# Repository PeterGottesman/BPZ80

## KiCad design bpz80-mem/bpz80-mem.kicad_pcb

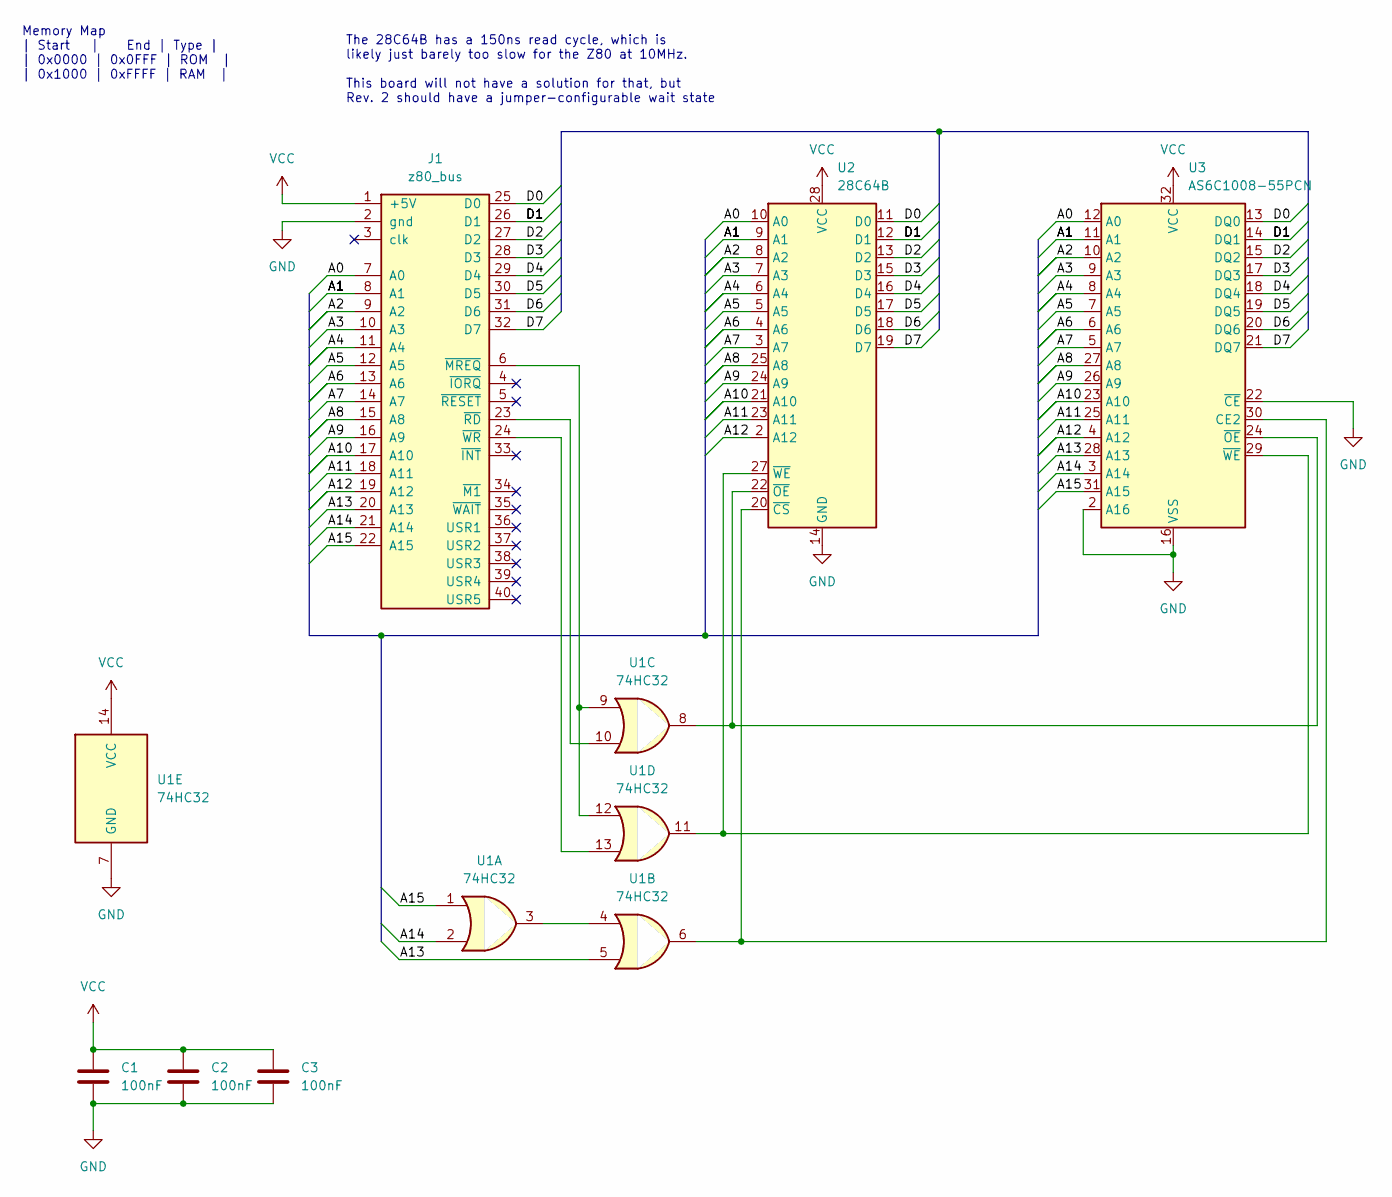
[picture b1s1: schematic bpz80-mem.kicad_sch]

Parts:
C1, C2, C3: 100nF; C_Disc_D5.0mm_W2.5mm_P5.00mm
J1: z80_bus; PinHeader_2x20_P2.54mm_Horizontal
U1: 74HC32; DIP-14_W7.62mm_Socket
U2: 28C64B; DIP-28_W15.24mm_Socket
U3: AS6C1008-55PCN; DIP-32_W15.24mm_Socket

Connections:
/A0: J1.7 (A0), U2.10 (A0), U3.12 (A0)
/A1: J1.8 (A1), U2.9 (A1), U3.11 (A1)
/A2: J1.9 (A2), U2.8 (A2), U3.10 (A2)
/A3: J1.10 (A3), U2.7 (A3), U3.9 (A3)
/A4: J1.11 (A4), U2.6 (A4), U3.8 (A4)
/A5: J1.12 (A5), U2.5 (A5), U3.7 (A5)
/A6: J1.13 (A6), U2.4 (A6), U3.6 (A6)
/A7: J1.14 (A7), U2.3 (A7), U3.5 (A7)
/A8: J1.15 (A8), U2.25 (A8), U3.27 (A8)
/A9: J1.16 (A9), U2.24 (A9), U3.26 (A9)
/A10: J1.17 (A10), U2.21 (A10), U3.23 (A10)
/A11: J1.18 (A11), U2.23 (A11), U3.25 (A11)
/A12: J1.19 (A12), U2.2 (A12), U3.4 (A12)
/A13: J1.20 (A13), U1.5, U3.28 (A13)
/A14: J1.21 (A14), U1.2, U3.3 (A14)
/A15: J1.22 (A15), U1.1, U3.31 (A15)
/D0: J1.25 (D0), U2.11 (D0), U3.13 (DQ0)
/D1: J1.26 (D1), U2.12 (D1), U3.14 (DQ1)
/D2: J1.27 (D2), U2.13 (D2), U3.15 (DQ2)
/D3: J1.28 (D3), U2.15 (D3), U3.17 (DQ3)
/D4: J1.29 (D4), U2.16 (D4), U3.18 (DQ4)
/D5: J1.30 (D5), U2.17 (D5), U3.19 (DQ5)
/D6: J1.31 (D6), U2.18 (D6), U3.20 (DQ6)
/D7: J1.32 (D7), U2.19 (D7), U3.21 (DQ7)
GND: C1.2, C2.2, C3.2, J1.2 (gnd), U1.7 (GND), U2.14 (GND), U3.2 (A16), U3.16 (VSS), U3.22 (~CE)
unnamed: J1.6 (~MREQ), U1.9, U1.12
unnamed: J1.23 (~RD), U1.10
unnamed: J1.24 (~WR), U1.13
unnamed: U1.3, U1.4
unnamed: U1.6, U2.20 (~CS), U3.30 (CE2)
unnamed: U1.8, U2.22 (~OE), U3.24 (~OE)
unnamed: U1.11, U2.27 (~WE), U3.29 (~WE)
VCC: C1.1, C2.1, C3.1, J1.1 (+5V), U1.14 (VCC), U2.28 (VCC), U3.32 (VCC)

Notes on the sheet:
Memory Map | Start | End | Type | | 0x0000 | 0x0FFF | ROM | | 0x1000 | 0xFFFF | RAM |
The 28C64B has a 150ns read cycle, which is likely just barely too slow for the Z80 at 10MHz. This board will not have a solution for that, but Rev. 2 should have a jumper-configurable wait state

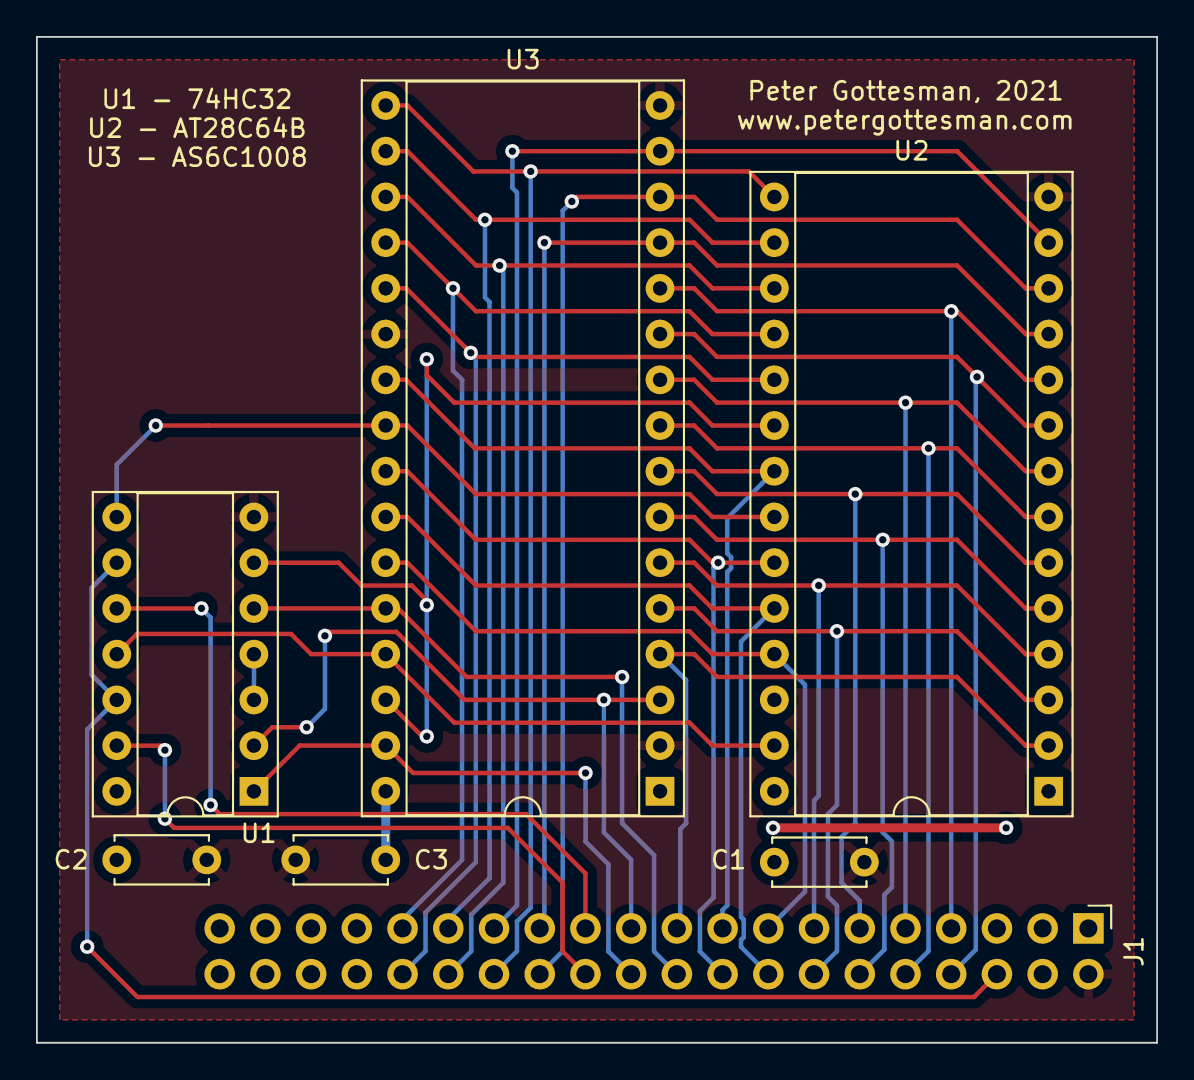
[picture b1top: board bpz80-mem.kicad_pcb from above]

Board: 2 copper layers, 62.2 x 55.9 mm, 7 parts (0 on the bottom side), 33 nets.

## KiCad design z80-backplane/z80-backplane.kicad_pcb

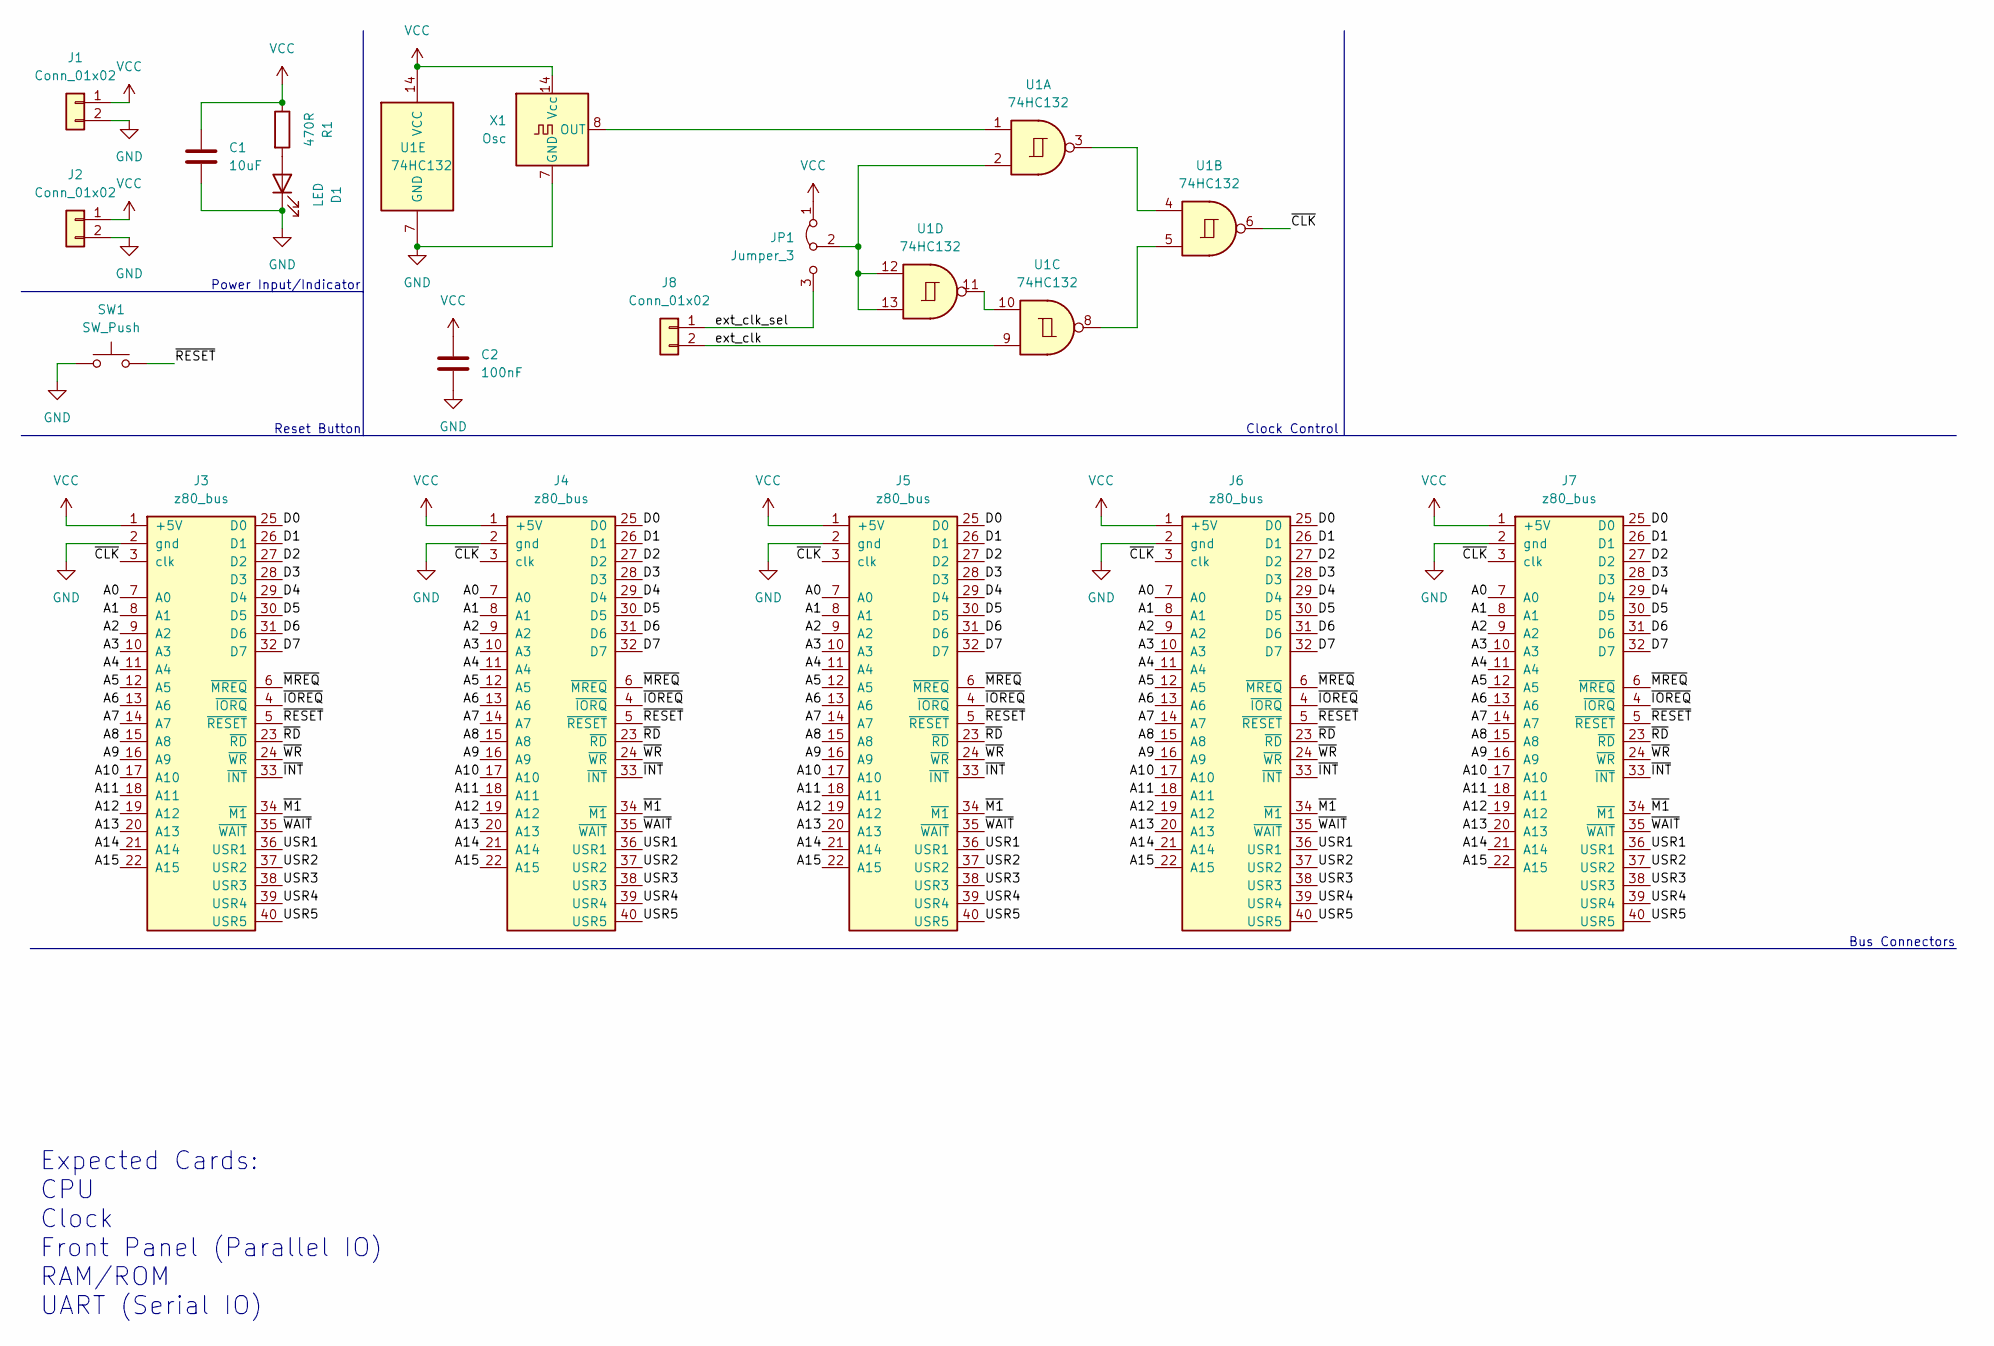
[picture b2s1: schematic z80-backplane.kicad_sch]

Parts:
C1: 10uF; C_Radial_D4.0mm_H5.0mm_P1.50mm
C2: 100nF; C_Disc_D5.0mm_W2.5mm_P5.00mm
D1: LED; LED_D4.0mm
J1: Conn_01x02; PinSocket_1x02_P2.54mm_Vertical
J2, J8: Conn_01x02; PinHeader_1x02_P2.54mm_Vertical
J3, J4, J5, J6, J7: z80_bus; PinSocket_2x20_P2.54mm_Vertical
JP1: Jumper_3; PinHeader_1x03_P2.54mm_Vertical
R1: 470R; R_Axial_DIN0207_L6.3mm_D2.5mm_P10.16mm_Horizontal
SW1: SW_Push; SW_PUSH_6mm
U1: 74HC132; DIP-14_W7.62mm_Socket
X1: Osc; Oscillator_DIP-14

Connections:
/A0: J3.7 (A0), J4.7 (A0), J5.7 (A0), J6.7 (A0), J7.7 (A0)
/A1: J3.8 (A1), J4.8 (A1), J5.8 (A1), J6.8 (A1), J7.8 (A1)
/A2: J3.9 (A2), J4.9 (A2), J5.9 (A2), J6.9 (A2), J7.9 (A2)
/A3: J3.10 (A3), J4.10 (A3), J5.10 (A3), J6.10 (A3), J7.10 (A3)
/A4: J3.11 (A4), J4.11 (A4), J5.11 (A4), J6.11 (A4), J7.11 (A4)
/A5: J3.12 (A5), J4.12 (A5), J5.12 (A5), J6.12 (A5), J7.12 (A5)
/A6: J3.13 (A6), J4.13 (A6), J5.13 (A6), J6.13 (A6), J7.13 (A6)
/A7: J3.14 (A7), J4.14 (A7), J5.14 (A7), J6.14 (A7), J7.14 (A7)
/A8: J3.15 (A8), J4.15 (A8), J5.15 (A8), J6.15 (A8), J7.15 (A8)
/A9: J3.16 (A9), J4.16 (A9), J5.16 (A9), J6.16 (A9), J7.16 (A9)
/A10: J3.17 (A10), J4.17 (A10), J5.17 (A10), J6.17 (A10), J7.17 (A10)
/A11: J3.18 (A11), J4.18 (A11), J5.18 (A11), J6.18 (A11), J7.18 (A11)
/A12: J3.19 (A12), J4.19 (A12), J5.19 (A12), J6.19 (A12), J7.19 (A12)
/A13: J3.20 (A13), J4.20 (A13), J5.20 (A13), J6.20 (A13), J7.20 (A13)
/A14: J3.21 (A14), J4.21 (A14), J5.21 (A14), J6.21 (A14), J7.21 (A14)
/A15: J3.22 (A15), J4.22 (A15), J5.22 (A15), J6.22 (A15), J7.22 (A15)
/D0: J3.25 (D0), J4.25 (D0), J5.25 (D0), J6.25 (D0), J7.25 (D0)
/D1: J3.26 (D1), J4.26 (D1), J5.26 (D1), J6.26 (D1), J7.26 (D1)
/D2: J3.27 (D2), J4.27 (D2), J5.27 (D2), J6.27 (D2), J7.27 (D2)
/D3: J3.28 (D3), J4.28 (D3), J5.28 (D3), J6.28 (D3), J7.28 (D3)
/D4: J3.29 (D4), J4.29 (D4), J5.29 (D4), J6.29 (D4), J7.29 (D4)
/D5: J3.30 (D5), J4.30 (D5), J5.30 (D5), J6.30 (D5), J7.30 (D5)
/D6: J3.31 (D6), J4.31 (D6), J5.31 (D6), J6.31 (D6), J7.31 (D6)
/D7: J3.32 (D7), J4.32 (D7), J5.32 (D7), J6.32 (D7), J7.32 (D7)
/USR1: J3.36 (USR1), J4.36 (USR1), J5.36 (USR1), J6.36 (USR1), J7.36 (USR1)
/USR2: J3.37 (USR2), J4.37 (USR2), J5.37 (USR2), J6.37 (USR2), J7.37 (USR2)
/USR3: J3.38 (USR3), J4.38 (USR3), J5.38 (USR3), J6.38 (USR3), J7.38 (USR3)
/USR4: J3.39 (USR4), J4.39 (USR4), J5.39 (USR4), J6.39 (USR4), J7.39 (USR4)
/USR5: J3.40 (USR5), J4.40 (USR5), J5.40 (USR5), J6.40 (USR5), J7.40 (USR5)
/ext_clk: J8.2, U1.9
/ext_clk_sel: J8.1, JP1.3 (B)
/~CLK: J3.3 (clk), J4.3 (clk), J5.3 (clk), J6.3 (clk), J7.3 (clk), U1.6
/~INT: J3.33 (~INT), J4.33 (~INT), J5.33 (~INT), J6.33 (~INT), J7.33 (~INT)
/~IOREQ: J3.4 (~IORQ), J4.4 (~IORQ), J5.4 (~IORQ), J6.4 (~IORQ), J7.4 (~IORQ)
/~M1: J3.34 (~M1), J4.34 (~M1), J5.34 (~M1), J6.34 (~M1), J7.34 (~M1)
/~MREQ: J3.6 (~MREQ), J4.6 (~MREQ), J5.6 (~MREQ), J6.6 (~MREQ), J7.6 (~MREQ)
/~RD: J3.23 (~RD), J4.23 (~RD), J5.23 (~RD), J6.23 (~RD), J7.23 (~RD)
/~RESET: J3.5 (~RESET), J4.5 (~RESET), J5.5 (~RESET), J6.5 (~RESET), J7.5 (~RESET), SW1.2
/~WAIT: J3.35 (~WAIT), J4.35 (~WAIT), J5.35 (~WAIT), J6.35 (~WAIT), J7.35 (~WAIT)
/~WR: J3.24 (~WR), J4.24 (~WR), J5.24 (~WR), J6.24 (~WR), J7.24 (~WR)
GND: C1.2, C2.2, D1.1 (K), J1.2, J2.2, J3.2 (gnd), J4.2 (gnd), J5.2 (gnd), J6.2 (gnd), J7.2 (gnd), SW1.1, U1.7 (GND), X1.7 (GND)
unnamed: D1.2 (A), R1.2
unnamed: JP1.2 (C), U1.2, U1.12, U1.13
unnamed: U1.1, X1.8 (OUT)
unnamed: U1.3, U1.4
unnamed: U1.5, U1.8
unnamed: U1.10, U1.11
VCC: C1.1, C2.1, J1.1, J2.1, J3.1 (+5V), J4.1 (+5V), J5.1 (+5V), J6.1 (+5V), J7.1 (+5V), JP1.1 (A), R1.1, U1.14 (VCC), X1.14 (Vcc)

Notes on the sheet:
Reset Button
Power Input/Indicator
Bus Connectors
Expected Cards: CPU Clock Front Panel (Parallel IO) RAM/ROM UART (Serial IO)
Clock Control

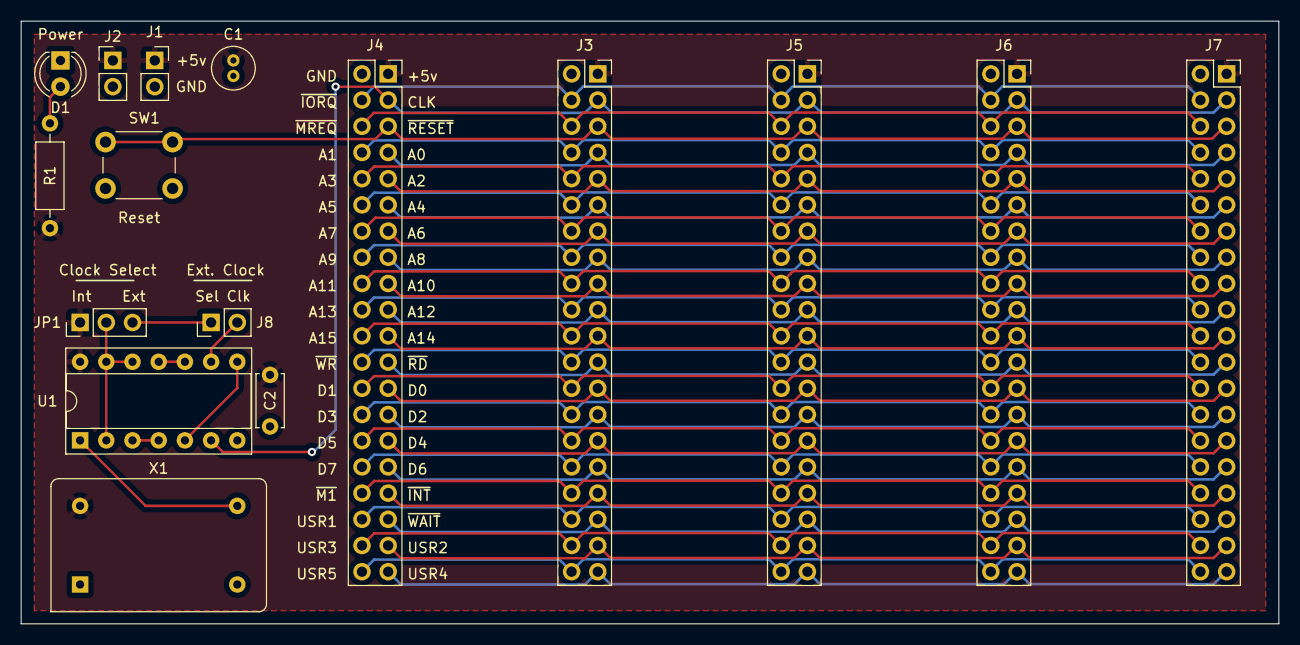
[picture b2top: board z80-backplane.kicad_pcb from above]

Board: 2 copper layers, 121.9 x 58.4 mm, 16 parts (0 on the bottom side), 48 nets.

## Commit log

2022-02-20 Initial commit, readme and renaming needed
